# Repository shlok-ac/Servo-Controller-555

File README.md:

# 555 Servo Controller

A 555 timer based servo controller designed in KiCad as part of my PCB design learning journey. The project focuses primarily on the PCB design workflow, including schematic and footprint selection, component placement, routing, 3D visualization, design-rule verification, and preparation of fabrication files.

> **Project status:** PCB design completed. The board has not been physically manufactured or tested.

> **[View Project Website →](https://shlok-ac.github.io/Servo-Controller-555/)**

## TL;DR

- Designed in **KiCad 10.0** as a PCB design learning project.
- Uses a **555 timer** to generate the servo control signal, with a potentiometer for adjustment.
- Includes the complete KiCad project, PCB documentation, 3D views, ERC/DRC reports, Gerbers, drill files, BOM, and position file.
- ERC and DRC checks completed with **0 errors and 0 warnings/violations**.
- The PCB has **not been physically manufactured or tested**.

## Quick Links

- [Schematic PDF](documentation/schematic.pdf)
- [PCB Layout PDF](documentation/pcb-layout.pdf)
- [Front 3D View](assets/pcb-3d-front.png)
- [Back 3D View](assets/pcb-3d-back.png)
- [Gerber Files](fabrication/gerbers/)
- [Drill Files](fabrication/drills/)
- [BOM](fabrication/BOM.csv)
- [Position / Pick-and-Place File](fabrication/position.csv)
- [ERC Report](documentation/verification/ERC.rpt)
- [DRC Report](documentation/verification/DRC.rpt)

---

## Overview

This project was created while working through the training modules by NU Teams.

The main goal was to practice the complete PCB design process in KiCad, including:

- Creating and working with a schematic
- Selecting and assigning footprints
- Designing the PCB layout
- Component placement and routing
- PCB mechanical considerations
- 3D visualization of the board
- Generating fabrication and assembly files
- Running ERC and DRC checks
- Organizing a complete KiCad project for sharing and reuse

The underlying circuit uses a 555 timer to generate the control signal for a servo. A potentiometer is used to adjust the generated pulse, allowing the servo position to be varied. The circuit is kept relatively simple here because the primary focus of this repository is the **PCB design and documentation workflow**.

---

## Repository Structure

<pre>
Servo-Controller-555/
│
├── <a href=".gitattributes">.gitattributes</a>
├── <a href=".gitignore">.gitignore</a>
├── <a href="LICENSE">LICENSE</a>
├── <a href="README.md">README.md</a>
├── <a href="index.html">index.html</a>
│
├── <a href="Servo%20Controller%20555.kicad_pcb">Servo Controller 555.kicad_pcb</a>
├── <a href="Servo%20Controller%20555.kicad_pro">Servo Controller 555.kicad_pro</a>
├── <a href="Servo%20Controller%20555.kicad_sch">Servo Controller 555.kicad_sch</a>
│
├── <a href="assets/">assets/</a>
│   ├── <a href="assets/pcb-3d-front.png">pcb-3d-front.png</a>
│   ├── <a href="assets/pcb-3d-back.png">pcb-3d-back.png</a>
│   ├── <a href="assets/schematic.png">schematic.png</a>
│   └── <a href="assets/pcb-layout.png">pcb-layout.png</a>
│
├── <a href="documentation/">documentation/</a>
│   ├── <a href="documentation/schematic.pdf">schematic.pdf</a>
│   ├── <a href="documentation/pcb-layout.pdf">pcb-layout.pdf</a>
│   └── <a href="documentation/verification/">verification/</a>
│       ├── <a href="documentation/verification/ERC.rpt">ERC.rpt</a>
│       └── <a href="documentation/verification/DRC.rpt">DRC.rpt</a>
│
├── <a href="fabrication/">fabrication/</a>
│   ├── <a href="fabrication/gerbers/">gerbers/</a>
│   ├── <a href="fabrication/drills/">drills/</a>
│   ├── <a href="fabrication/BOM.csv">BOM.csv</a>
│   └── <a href="fabrication/position.csv">position.csv</a>
│
└── <a href="external-cad/">external-cad/</a>
    └── <a href="external-cad/Potentiometer_Bourns_PTV09A-1_Single_Vertical.step">Potentiometer_Bourns_PTV09A-1_Single_Vertical.step</a>
</pre>

---

## Features

- 555 timer based servo controller
- Adjustable servo control using a potentiometer
- Through-hole and SMD components
- Custom component footprints
- 3D PCB visualization
- External STEP model for component visualization
- ERC and DRC verification
- Fabrication-ready Gerber and drill files
- Bill of Materials (BOM)
- Component position / Pick-and-Place file

---

## PCB Design

The PCB was designed with emphasis on:

- Component placement
- Routing and trace organization
- Connector accessibility
- Mounting-hole placement
- Board outline and mechanical clearances
- Clear silkscreen labeling
- 3D representation of the completed PCB design

### PCB Layout

[View PCB Layout PDF](documentation/pcb-layout.pdf)

### Footprints & Libraries

The project uses KiCad libraries and project-defined footprints for the components used on the PCB.

- Standard KiCad footprints are used where applicable.
- Custom footprints are included as part of the project where required.
- The PCB project contains the footprint assignments used by the design.
- The external 3D model used by the potentiometer footprint is documented separately in [External CAD Models](#external-cad-models).

If the project is edited or reused, footprint assignments should be checked in the schematic and PCB files before making design changes.

### 3D Views

<details>
<summary>View Front 3D Model</summary>

</details>

<details>
<summary>View Back 3D Model</summary>

</details>

---

## Circuit Overview

The circuit is based around a 555 timer configured to generate a servo control signal.

A potentiometer is used to vary the timing of the generated pulse, allowing the servo position to be adjusted.

The schematic is included primarily to document the electrical design associated with the PCB.

### Schematic

[View Schematic PDF](documentation/schematic.pdf)

---

## Design Verification

The design was checked using KiCad's Electrical Rules Checker (ERC) and Design Rules Checker (DRC).

### ERC

- Errors: **0**
- Warnings: **0**

[View ERC Report](documentation/verification/ERC.rpt)

### DRC

- Violations: **0**
- Unconnected pads: **0**
- Footprint errors: **0**

[View DRC Report](documentation/verification/DRC.rpt)

> These checks verify the design according to the configured KiCad rules. They do not replace physical testing of a manufactured PCB.

---

## Fabrication Files

Although this PCB has **not been physically manufactured**, the repository contains the files generated during the design process for potential future fabrication and assembly.

<details>
<summary>Available fabrication files</summary>

### Gerbers

PCB manufacturing files generated from the PCB layout.

[Open Gerber files](fabrication/gerbers/)

### Drill Files

Drill data generated for the PCB.

[Open drill files](fabrication/drills/)

### Bill of Materials

Component list generated from the KiCad project.

[View BOM](fabrication/BOM.csv)

### Position File

Component placement information generated from the PCB design.

[View Position File](fabrication/position.csv)

</details>

---

## External CAD Models

The PCB uses an external STEP model for component visualization in KiCad's 3D Viewer.

The model is stored separately from the KiCad project files:

```text
external-cad/
└── Potentiometer_Bourns_PTV09A-1_Single_Vertical.step
```

The PCB references the model using a project-relative path, so the reference should remain valid when the repository is cloned to another system.

> The redistribution rights of externally sourced CAD models depend on their original license/source. The external model is therefore treated separately from the project's own hardware design files.

---

## Working with the Project

This repository contains the complete KiCad project, including the schematic, PCB layout, project configuration, and supporting project assets.

### Requirements

- **KiCad 10.0** or a compatible version capable of opening the project files.

### Clone the Repository

To clone the project using Git:

```bash
git clone https://github.com/shlok-ac/Servo-Controller-555.git
cd Servo-Controller-555
```

Or use the [GitHub repository page](https://github.com/shlok-ac/Servo-Controller-555) to download the project as a ZIP archive.

### Open in KiCad

1. Clone or download this repository.
2. Open `Servo Controller 555.kicad_pro` in KiCad.
3. From the KiCad Project Manager, open the **Schematic Editor** or **PCB Editor** as required.

The schematic, PCB layout, and project configuration files are kept together so that the project can be opened and edited as a complete KiCad project after cloning.

### Project Files

The main KiCad files are:

- `Servo Controller 555.kicad_pro` — KiCad project configuration
- `Servo Controller 555.kicad_sch` — schematic
- `Servo Controller 555.kicad_pcb` — PCB layout

See [External CAD Models](#external-cad-models) for the STEP model used by the PCB's 3D visualization.

---

## Learning Source

This project was completed while working through the PCB Design Zero-to-Hero training modules by **NU Teams**.

The training material provided the learning framework for the project, while this repository contains my KiCad project files, PCB layout, documentation, verification results, and generated fabrication outputs.

---

## License

Copyright © 2026 Shlok Chorge

This project is licensed under the **CERN Open Hardware Licence Version 2 – Strongly Reciprocal (CERN-OHL-S-2.0)**.

This license allows others to:

- Use and study the hardware design
- Modify and adapt the design
- Manufacture hardware based on the design
- Distribute the original or modified design

Under the Strongly Reciprocal terms, modifications and derivative designs based on this project must be made available under the same license, along with the corresponding source design files.

See [`LICENSE`](LICENSE) for the complete license text.

---

## Author

**Shlok Chorge** · [GitHub Profile](https://github.com/shlok-ac)

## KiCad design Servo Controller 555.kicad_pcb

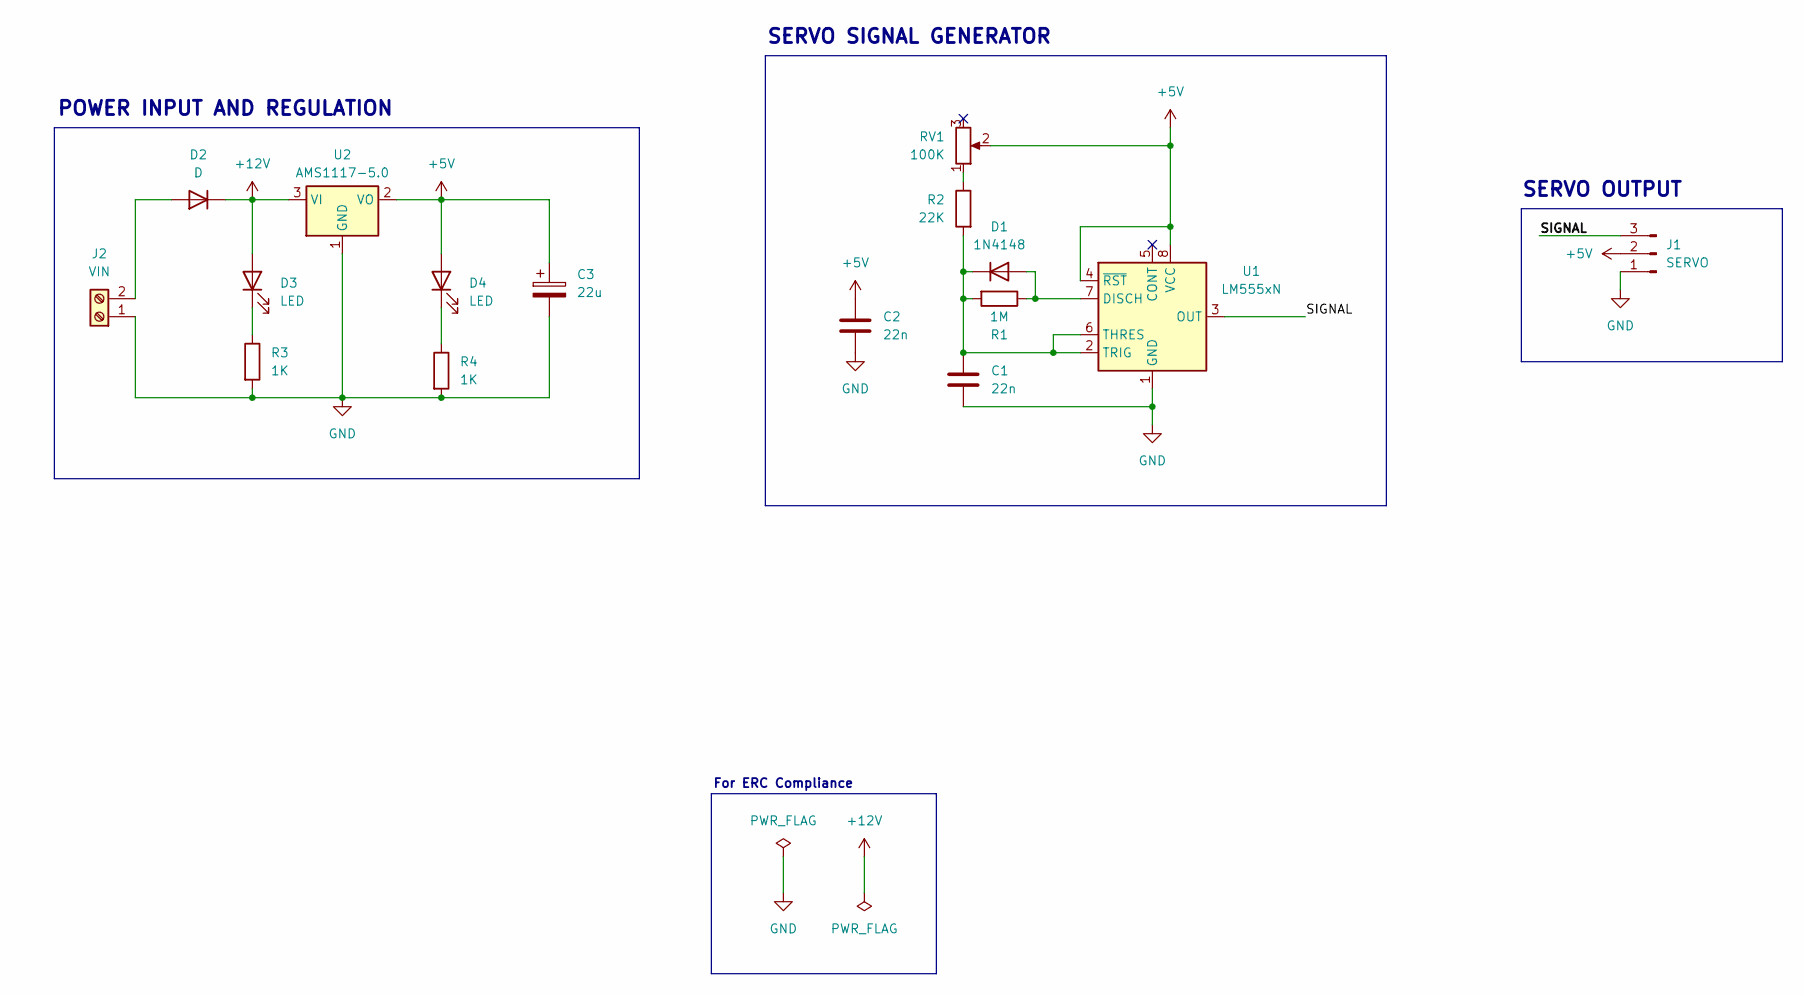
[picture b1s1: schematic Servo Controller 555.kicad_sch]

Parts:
C1, C2: 22n; C_Disc_D3.8mm_W2.6mm_P2.50mm
C3: 22u; C_0805_2012Metric_Pad1.18x1.45mm_HandSolder
D1: 1N4148; D_DO-35_SOD27_P7.62mm_Horizontal
D2: D; D_SMA_Handsoldering
D3: LED; LED_0805_2012Metric_Pad1.15x1.40mm_HandSolder
D4: LED; LED_D5.0mm
J1: SERVO; PinHeader_1x03_P2.54mm_Vertical
J2: VIN; TerminalBlock_Phoenix_MKDS-1,5-2_1x02_P5.00mm_Horizontal
R1: 1M; R_Axial_DIN0204_L3.6mm_D1.6mm_P7.62mm_Horizontal
R2: 22K; R_Axial_DIN0204_L3.6mm_D1.6mm_P7.62mm_Horizontal
R3: 1K; R_1206_3216Metric
R4: 1K; R_Axial_DIN0204_L3.6mm_D1.6mm_P7.62mm_Horizontal
RV1: 100K; Potentiometer_Bourns_PTV09A-1_Single_Vertical
U1: LM555xN; DIP-8_W7.62mm
U2: AMS1117-5.0; SOT-223-3_TabPin2

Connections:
+5V: C2.1, C3.1, D4.2 (A), J1.2, RV1.2, U1.4 (~RST), U1.8 (VCC), U2.2 (VO)
+12V: D2.1 (K), D3.2 (A), U2.3 (VI)
/SIGNAL: J1.3, U1.3 (OUT)
GND: C1.2, C2.2, C3.2, J1.1, J2.1, R3.2, R4.2, U1.1 (GND), U2.1 (GND)
unnamed: D1.2 (A), R1.1, U1.7 (DISCH)
unnamed: C1.1, D1.1 (K), R1.2, R2.2, U1.2 (TRIG), U1.6 (THRES)
unnamed: D2.2 (A), J2.2
unnamed: D3.1 (K), R3.1
unnamed: D4.1 (K), R4.1
unnamed: R2.1, RV1.1

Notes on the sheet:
POWER INPUT AND REGULATION
For ERC Compliance
SERVO OUTPUT
SERVO SIGNAL GENERATOR

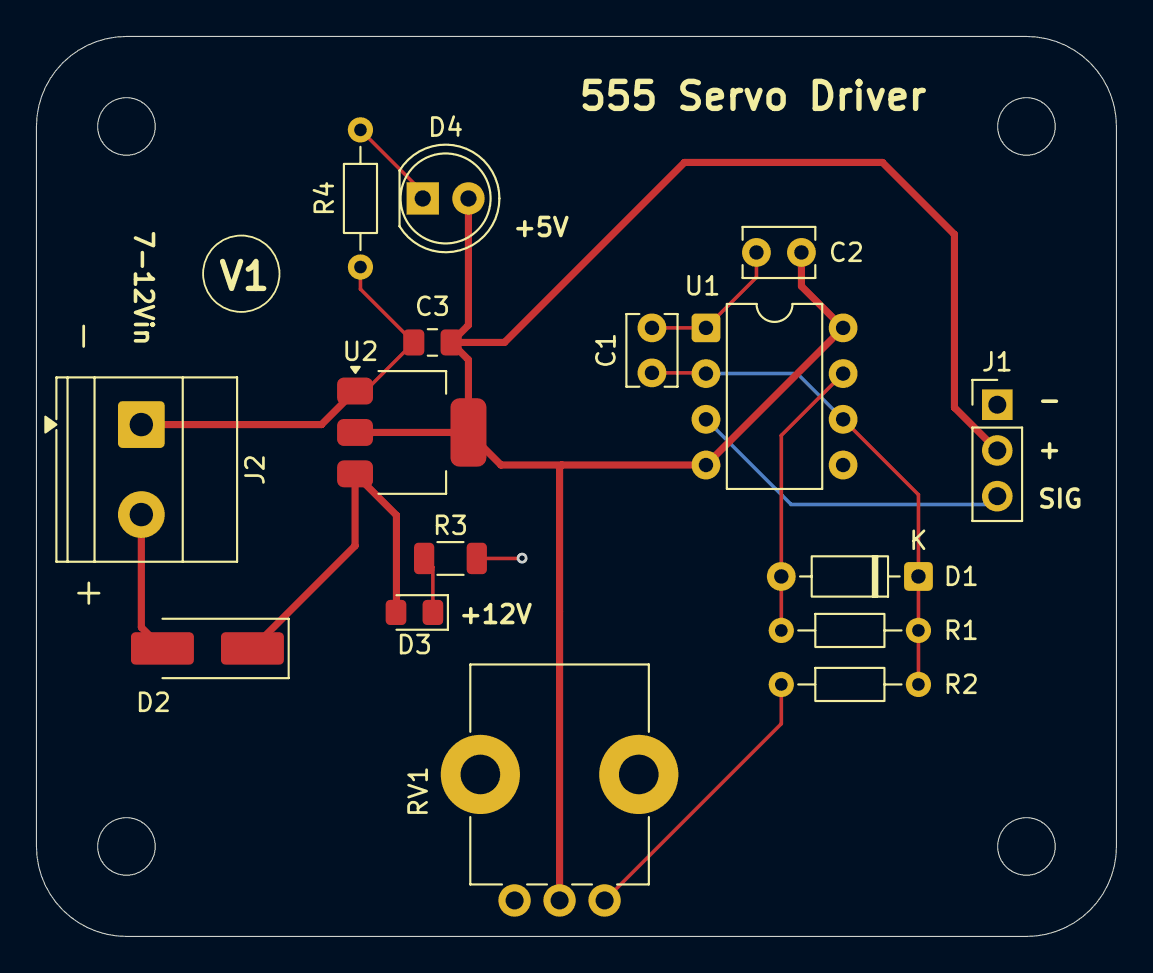
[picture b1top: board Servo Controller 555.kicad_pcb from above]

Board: 2 copper layers, 60.0 x 50.0 mm, 16 parts (0 on the bottom side), 10 nets.

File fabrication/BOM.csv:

"#","Reference","Qty","Value","DNP","Exclude from BOM","Exclude from Board","Footprint","Datasheet"
"1","C1,C2","2","22n","","","","Capacitor_THT:C_Disc_D3.8mm_W2.6mm_P2.50mm",""
"2","C3","1","22u","","","","Capacitor_SMD:C_0805_2012Metric_Pad1.18x1.45mm_HandSolder",""
"3","D1","1","1N4148","","","","Diode_THT:D_DO-35_SOD27_P7.62mm_Horizontal",""
"4","D2","1","D","","","","Diode_SMD:D_SMA_Handsoldering",""
"5","D3","1","LED","","","","LED_SMD:LED_0805_2012Metric_Pad1.15x1.40mm_HandSolder",""
"6","D4","1","LED","","","","LED_THT:LED_D5.0mm",""
"7","J1","1","SERVO","","","","Connector_PinHeader_2.54mm:PinHeader_1x03_P2.54mm_Vertical",""
"8","J2","1","VIN","","","","TerminalBlock_Phoenix:TerminalBlock_Phoenix_MKDS-1,5-2_1x02_P5.00mm_Horizontal",""
"9","R1","1","1M","","","","Resistor_THT:R_Axial_DIN0204_L3.6mm_D1.6mm_P7.62mm_Horizontal",""
"10","R2","1","22K","","","","Resistor_THT:R_Axial_DIN0204_L3.6mm_D1.6mm_P7.62mm_Horizontal",""
"11","R3","1","1K","","","","Resistor_SMD:R_1206_3216Metric",""
"12","R4","1","1K","","","","Resistor_THT:R_Axial_DIN0204_L3.6mm_D1.6mm_P7.62mm_Horizontal",""
"13","RV1","1","100K","","","","Potentiometer_THT:Potentiometer_Bourns_PTV09A-1_Single_Vertical",""
"14","U1","1","LM555xN","","","","Package_DIP:DIP-8_W7.62mm","http://www.ti.com/lit/ds/symlink/lm555.pdf"
"15","U2","1","AMS1117-5.0","","","","Package_TO_SOT_SMD:SOT-223-3_TabPin2","http://www.advanced-monolithic.com/pdf/ds1117.pdf"

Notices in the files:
README.md:
License: CERN-OHL-S-2.0
